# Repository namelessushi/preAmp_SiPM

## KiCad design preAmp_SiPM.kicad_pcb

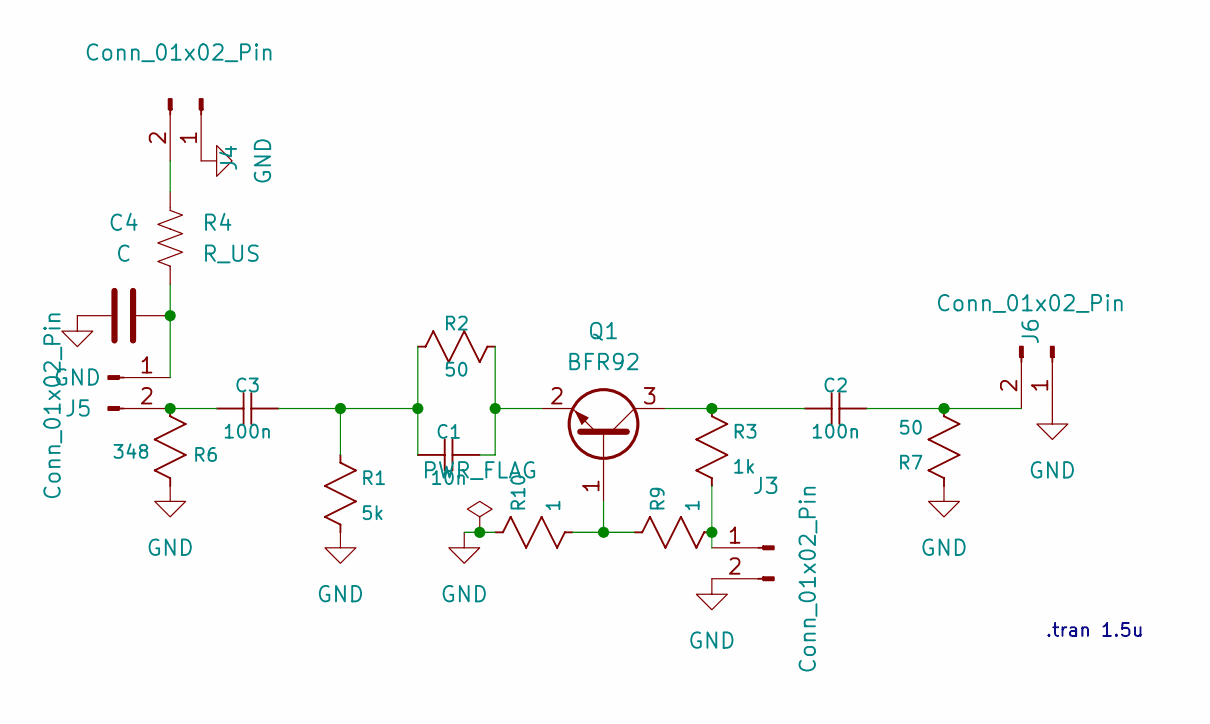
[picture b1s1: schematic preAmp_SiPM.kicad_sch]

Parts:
C1: 10n; C_0805_2012Metric_Pad1.18x1.45mm_HandSolder
C2, C3: 100n; C_0805_2012Metric_Pad1.18x1.45mm_HandSolder
C4: C; C_0805_2012Metric_Pad1.18x1.45mm_HandSolder
J3, J4, J5, J6: Conn_01x02_Pin; PinHeader_1x02_P2.54mm_Vertical
Q1: BFR92; SOT65P210X100-3N
R1: 5k; R_0805_2012Metric_Pad1.20x1.40mm_HandSolder
R2, R7: 50; R_0805_2012Metric_Pad1.20x1.40mm_HandSolder
R3: 1k; R_0805_2012Metric_Pad1.20x1.40mm_HandSolder
R4: R_US; R_0805_2012Metric_Pad1.20x1.40mm_HandSolder
R6: 348; R_0805_2012Metric_Pad1.20x1.40mm_HandSolder
R9, R10: 1; R_0805_2012Metric_Pad1.20x1.40mm_HandSolder

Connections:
GND: C4.1, J3.2, J4.1, J6.1, R1.2, R6.2, R7.1, R10.1
unnamed: C1.2, C3.1, R1.1, R2.2
unnamed: J3.1, R3.2, R9.2
unnamed: J4.2, R4.1
unnamed: C4.2, J5.1, R4.2
unnamed: C3.2, J5.2, R6.1
unnamed: C2.1, J6.2, R7.2
unnamed: Q1.1 (B), R9.1, R10.2
unnamed: C2.2, Q1.3 (C), R3.1
unnamed: C1.1, Q1.2 (E), R2.1

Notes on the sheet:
.tran 1.5u

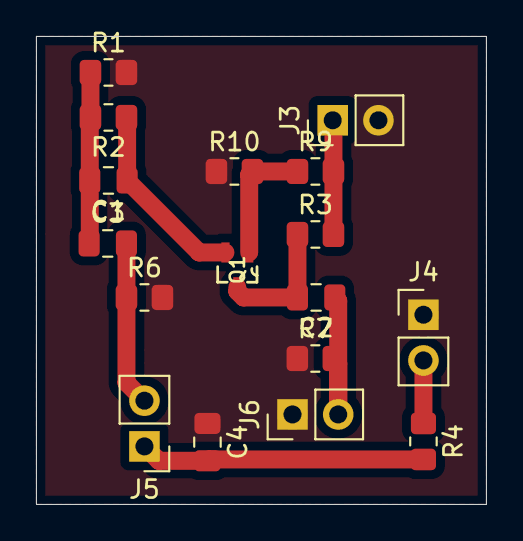
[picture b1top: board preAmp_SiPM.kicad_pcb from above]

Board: 2 copper layers, 25.0 x 26.0 mm, 17 parts (0 on the bottom side), 10 nets.
